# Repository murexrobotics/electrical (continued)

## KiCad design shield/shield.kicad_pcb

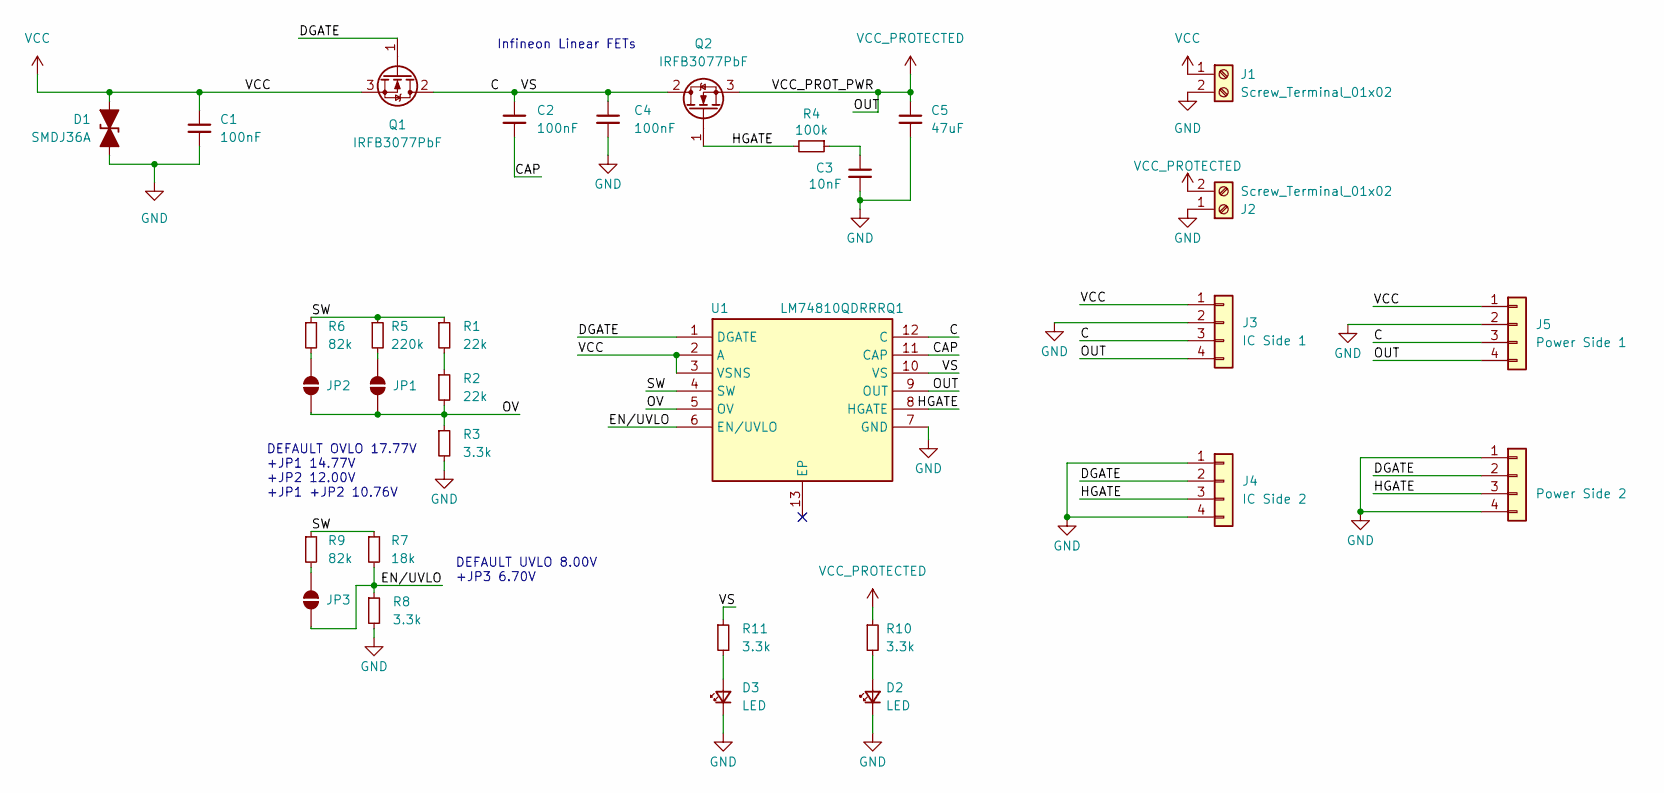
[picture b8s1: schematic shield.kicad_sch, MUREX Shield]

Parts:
C1, C2, C4: 100nF; C_0603_1608Metric
C3: 10nF; C_0603_1608Metric
C5: 47uF; C_1206_3216Metric
D1: SMDJ36A; D_SMC
D2, D3: LED; LED_0603_1608Metric
J1, J2: Screw_Terminal_01x02; TerminalBlock_Phoenix_MKDS-1,5-2-5.08_1x02_P5.08mm_Horizont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
J3: IC Side 1; PinHeader_1x04_P2.54mm_Vertical
J4: IC Side 2; PinHeader_1x04_P2.54mm_Vertical
J5: Power Side 1; PinHeader_1x04_P2.54mm_Vertical
J6: Power Side 2; PinHeader_1x04_P2.54mm_Vertical
JP1, JP2, JP3: SolderJumper_2_Open; SolderJumper-2_P1.3mm_Open_RoundedPad1.0x1.5mm
Q1, Q2: IRFB3077PbF; PG-TO220-3_INF
R1, R2: 22k; R_0603_1608Metric
R3, R8, R10, R11: 3.3k; R_0603_1608Metric
R4: 100k; R_0603_1608Metric
R5: 220k; R_0603_1608Metric
R6, R9: 82k; R_0603_1608Metric
R7: 18k; R_0603_1608Metric
U1: LM74810QDRRRQ1; SON50P300X300X80-13N-D; Manufacturer_Part_Number LM74810QDRRRQ1; Mouser Part Number 595-LM74810QDRRRQ1

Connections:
/C: C2.1, C4.1, J3.3, J5.3, Q1.2 (D), Q2.2 (D), R11.1, U1.10 (VS), U1.12 (C)
/CAP: C2.2, U1.11 (CAP)
/DGATE: J4.2, J6.2, Q1.1 (G), U1.1 (DGATE)
/EN/UVLO: JP3.2 (B), R7.2, R8.1, U1.6 (EN/UVLO)
/HGATE: J4.3, J6.3, Q2.1 (G), R4.2, U1.8 (HGATE)
/OV: JP1.2 (B), JP2.2 (B), R2.2, R3.1, U1.5 (OV)
/SW: R1.1, R5.1, R6.1, R7.1, R9.1, U1.4 (SW)
GND: C1.2, C3.2, C4.2, C5.2, D1.1 (A1), D2.1 (K), D3.1 (K), J1.2, J2.1, J3.2, J4.1, J4.4, J5.2, J6.1, J6.4, R3.2, R8.2, U1.7 (GND)
unnamed: C3.1, R4.1
unnamed: D2.2 (A), R10.2
unnamed: D3.2 (A), R11.2
unnamed: JP1.1 (A), R5.2
unnamed: JP2.1 (A), R6.2
unnamed: JP3.1 (A), R9.2
unnamed: R1.2, R2.1
VCC: C1.1, D1.2 (A2), J1.1, J3.1, J5.1, Q1.3 (S), U1.2 (A), U1.3 (VSNS)
VCC_PROTECTED: C5.1, J2.2, J3.4, J5.4, Q2.3 (S), R10.1, U1.9 (OUT)

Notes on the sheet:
DEFAULT OVLO 17.77V +JP1 14.77V +JP2 12.00V +JP1 +JP2 10.76V
Infineon Linear FETs
DEFAULT UVLO 8.00V +JP3 6.70V

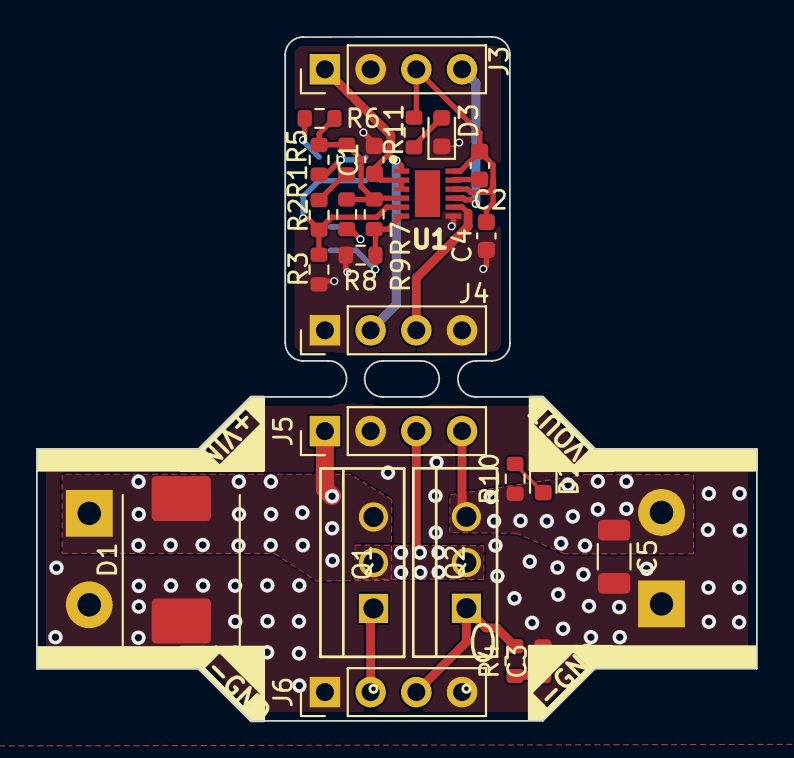
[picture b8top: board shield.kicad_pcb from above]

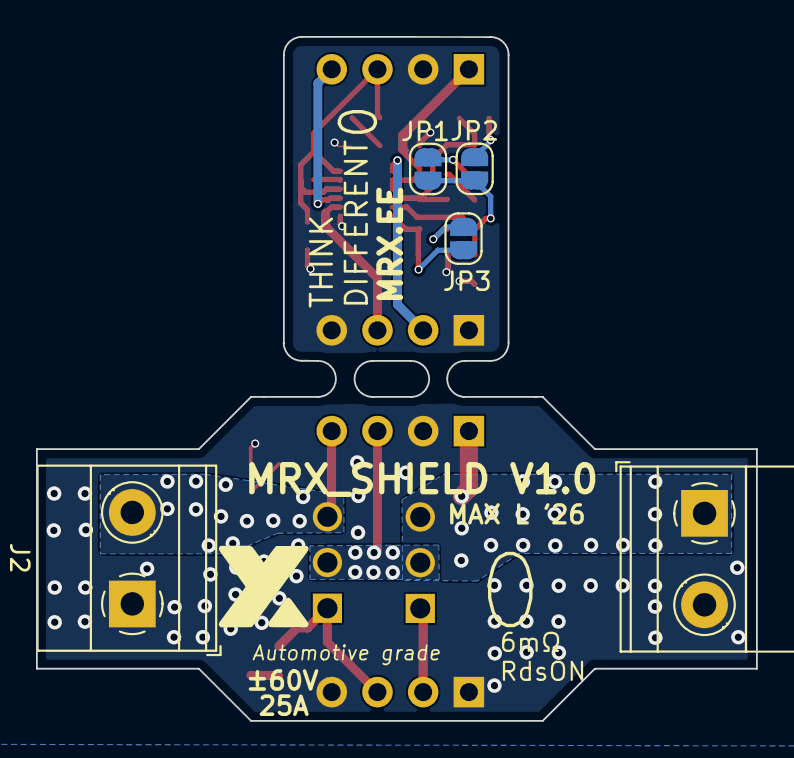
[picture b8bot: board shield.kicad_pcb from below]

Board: 2 copper layers, 40.0 x 38.0 mm, 31 parts (5 on the bottom side), 17 nets.

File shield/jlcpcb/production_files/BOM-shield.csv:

Comment,Designator,Footprint,LCSC
100nF,"C1,C2,C4",C_0603_1608Metric,C14663
SMDJ36A,D1,D_SMC,C152051
LED,D2,LED_0603_1608Metric,C2286
220k,R5,R_0603_1608Metric,C22961
LED,D3,LED_0603_1608Metric,C2297
3.3k,"R10,R11,R3,R8",R_0603_1608Metric,C22978
82k,"R6,R9",R_0603_1608Metric,C23254
100k,R4,R_0603_1608Metric,C25803
18k,R7,R_0603_1608Metric,C25810
22k,"R1,R2",R_0603_1608Metric,C31850
LM74810QDRRRQ1,U1,SON50P300X300X80-13N-D,C3215601
10nF,C3,C_0603_1608Metric,C57112
47uF,C5,C_1206_3216Metric,C76659

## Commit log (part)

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2023-05-05 Feat: Created ESC Project
2023-05-05 Fix: Fix ESC project layout
2023-05-06 Feat: created CM4 schematic with modifications to fit needs
2023-05-07 Fix: added ds_store and auto save files to gitignore
2023-05-07 Feat: Added BMI088 to library
2023-05-07 Feat: added MMC5603NJ library
2023-05-07 Feat: carrier board synchronized footprints with schematic
2023-05-07 Feat: Attempted to add TPS568230 library (+ custom symbol)
2023-05-07 Fix: added footprint of TPS568230
2023-05-07 Feat: Removed TPS568230, added TPS568215RNNR symbol to library
2023-05-07 Fix: added whitespace in readme
2023-05-07 Feat: Added RP2040 (not connected yet), connectors
2023-05-07 Feat: initialized PLC project
2023-05-10 Feat: Added LTC4352 Symbol and Footprint
2023-05-10 Fix: Reworked LTC4352 Symbol
2023-05-11 Feat: Added Application Circuit for LTC4352
2023-05-12 Fix: added jumpers to all i2c sensors
2023-05-12 Feat: Configured VOUTs for both TPS568215s
2023-05-13 Feat: draft of ESC carrier board schematic
2023-05-13 Refactor: deleted unused hierarchical schematics
2023-05-14 Refactor/Feat: refactored projects into networking folder and created rj45_breakout project
2023-05-14 Fix: relinked footprints
2023-05-15 Feat: Added 01x03 Conn. for Power to ESC_Carrier
2023-05-15 Refactor: Moved bucks into hierarchical schematics
2023-05-15 Feat: begun work on carrier pcb and imported NGFF m.2 library
2023-05-16 Feat: imported m.2 connector and more work on carrier board
2023-05-16 Feat: organized PCB file, preparing for layout and routing.
2023-05-16 Fix: Altered M.2 Pinout
2023-05-17 Feat: Added Custom Softstarter Circuitry (C&R TBC)
2023-05-18 Feat: Added draft resistance and capacitance to softstarter
2023-05-19 Feat: Added ACS712 Current Sensor
2023-05-19 Feat: progress routing usb and hdmi
2023-05-19 Fix: added rounded corners and a few minor fixes
2023-05-20 Feat: more routing with i2c and gpio
2023-05-21 FEAT: added fuses to ESC Carrier
2023-05-22 FEAT: added efuses to ESC Carrier
2023-05-22 Refactor: moved custom symbol to library file
2023-05-23 feat: carrier board layout v2
2023-05-29 Feat: routed non-important traces on carrier board
2023-05-30 Feat: power line routing, marked down necessary revisions, rerouted i2c
2023-05-30 Feat: updated efuse symbol and assigned some footprints
2023-06-04 Fix: updated esc carrier to esc connectors
2023-06-04 Feat: impedanced matched traces calculations entered into net classes
2023-06-04 Feat: routed differential pairs. 90 more routes to go
2023-06-05 Fix: added phases to esc to esc carrier connector
2023-06-05 Feat: added test points
2023-06-05 Feat: updated esc to esc carrier connector, updated test points
2023-06-05 Refactor: component orientation
2023-06-05 Feat: conforms to jlc specs and (mostly) kicad DRC
2023-06-06 Feat: added murex font
2023-06-06 Feat: initial placement of components
2023-06-07 Feat: added silkscreen
2023-06-07 Feat: semi-baked adc implementation
2023-06-09 Feat: added some traces between components
2023-06-15 Feat: linked up majority of components to lcsc parts
2023-06-16 Feat: fixes all around, refactored project and working on CM4 POS file
2023-06-16 Refactor: re-annotated schematic with cm4 connector POS configured
2023-06-17 Feat: major revamps to pcb, finished bom and pos
2023-06-19 Feat: tidied up carrier board, added 3d models, fully prepared for production
2023-06-19 Feat: worked on ESC Carrier board
2023-06-20 Feat: Completed footprint assignment, began part placement
2023-06-20 Feat: small changes to carrier (i think units?)
2023-06-21 Feat: Finished layout for individual ICs
2023-06-24 Feat: Added 282836-2 (Backup Screw Term. to Carrier)
2023-06-25 Feat: finished routing esc carrier
2023-06-25 Feat: cleaned up traces and zones, adjusted trace widths
2023-06-26 Feat: Added copper zones for voltage regulation
2023-06-26 Fix: Minor Schematic Changes
2023-06-26 Feat: More routing and component rearranging
2023-06-26 Fix: Removed pull up resistors
2023-06-27 Feat: Finished routing
2023-06-28 Fix: added ADC I2C address to back silk
2023-07-03 Feat: 🎉🙏 carrier board v1 sent to production
2023-07-03 Fix: replace jlcpcb part no for R11 and R12
2023-07-03 Feat: Switched WAGO 2606-1103 to MOLEX 0430450821
2023-07-03 Feat: Reduced inductor pad size
2023-07-03 Feat: Deleted all traces, zones, and edge cuts
2023-07-04 Feat: routed traces
2023-07-04 Feat: routed phases
2023-07-04 Feat: carrier board v1.1 release and production
2023-07-04 Feat: generating v1.1 carrier board
2023-07-04 Revert "Feat: added vias"
    This reverts commit d9f0b0a7b740c1a5059e2e7f1ed87a6101a3388b.
2023-07-05 Feat: Basic silkscreening
2023-07-05 Feat: switched phase connector to microfit, updated esc connector pinout, updated component layout
2023-07-06 Feat: Updated board constraints, fixed various violations
2023-07-06 Feat: Added jumper for INA226
2023-07-07 Feat: Finished bom and cpl, generated gerbers
2023-07-10 Fix[carrier v1.2]: updated 5V zone for m.2
2023-07-11 Feat: Changed microfit pinout, added copper zone over vin
2023-07-11 Feat: Increased voltage output to 5.1V, edited back silkscreen
2023-07-11 Refactor: organized escs
2023-07-12 Fix: updated uart connections to carrier board
2023-07-12 Feat: initialized rp2040 esc and 5530843-7 card edge footprint
2023-07-14 Feat: Restructured labels, fixed nmos polarity, rerouted board
2023-07-15 Feat: Switched to Molex Megafit, Rerouting, Updated Silkscreen
2023-07-15 Feat: Updated schematic, minor silkscreen edits
2023-07-15 Feat: removed 7 ntc thermistors
2023-07-16 Feat: Created AGND islands
2023-07-16 Fix[carrier1.2]: kicad wants rotation?
2023-07-18 Feat: switched thermistor to AS32_1R030, minor fixes
2023-07-20 Feat: Removed ACS712 and M.2 Conn
2023-07-20 Feat: Broke out I2C
2023-07-20 Feat: created production files
2023-07-22 Feat: Powerboard sent to chinese production
2023-07-24 Feat: added 3d models
2023-07-29 Feat[esc]: schematic to pcb placement of B-G431B-ESC1 + RP2040
2023-07-29 Feat[stesc]: refactored project and finished draft
2023-08-03 Feat[esc_carrier 1.1]: refactored pinout to esc, made board smaller
2023-08-03 Fix: removed esc_carrier v1.0, removed blender files
2023-08-17 Feat[drvesc]: Established basic gate driver architecture
2023-08-18 Feat[bmi088 breakout]: design complete
2023-08-18 Feat[bme680 breakout]: design complete
2023-08-18 Feat[pca9585 breakout]: design complete
2023-08-19 Feat: Finished RP2040 control system
2023-08-20 Feat[drvesc]: Draft routing
2023-08-21 Feat[esc_carrier v2.0]: v2.0 production ready
2023-08-23 Feat[power]: Added LED 3D models
2023-08-24 Feat[drvesc]: updated card edge pinout
2023-08-25 Feat[drvesc]: Minor rerouting and positioning
2023-08-31 Feat[switch]: added IP175G symbol
2023-08-31 Feat[switch]: added sheet metadata and magnetics symbols to sch
2023-08-31 Feat[switch]: further work on schematic
2023-08-31 Fix[switch]: renamed quad to dual transformer
2023-09-01 Feat[anyesc]: initialized project
2023-09-01 Feat[switch]: unpolished schematic complete
2023-09-01 Feat[drvesc]: minor silkscreen edit
2023-09-01 Refactor[switch]: net labels and reorganisation
2023-09-01 Feat[switch]: created all necessary symbols and footprints, started PCB
2023-09-02 Feat[switch]: initial board layout (FOLLOW @TODOs)
2023-09-03 Feat[anyesc]: anyesc design complete
2023-09-16 Feat[switch]: initial routes
2023-09-25 Feat[switch]: Minor rerouting
2023-09-29 Feat[switch]: rotated J1
2023-10-06 Feat[breakouts]: created ina226 breakout schematic v1.0
2023-10-07 Feat[breakouts]: Fixed listed problems with ina226 breakout
2023-10-07 Feat[breakouts]: Separated A1/A0 from main chip schem
2023-10-07 Fix[ina226 breakout]: removed lock file
2023-10-08 Feat[switch]: Fixed single transformer footprint, added 3d models
2023-10-08 Feat[switch]: Added diode, initial silkscreen
2023-10-09 Feat[breakouts]: Created PCB layout, some ratsnest untangling
2023-10-09 Feat[breakouts]: Finished PCB layout for INA226
2023-10-09 Feat[breakouts]: Finished PCB layout for INA226, added traces
2023-10-10 Feat[breakouts]: Modified PCB layout, added some traces
2023-10-12 Feat[breakouts]: Added via stitching, rearranged some components, added copper pours
2023-10-16 Chore[bmi088 breakout]: bumped to new kicad version
2023-10-16 Chore[carrier]: bumped to new kicad version
2023-10-18 Feat[breakouts]: Moved header pins, added silk labelling, fixed 3d model?
2023-10-18 Feat[drvesc]: Tapeout
2023-10-18 Feat[anyesc]: tapeout
2023-10-19 Feat[breakouts]: Fixed silk, increased board size
2023-10-30 Anyesc tape out (panelization needs fixing)
2023-10-30 Feat[breakouts]: started ADC schematic
2023-10-30 Fix[anyesc]: panelization
2023-11-03 Feat[switch]: Minor fixes for tapeout
2023-11-10 Feat: Updated T3 part, ordered switch
2023-11-21 Feat[drvesc]: Fixed clearance violations
2023-11-25 Feat[carrier]: v3 schematic progress (esp32, general cleanup/refactoring)
2023-11-26 Feat[carrier]: v3 schematic draft complete
2023-11-26 Feat[power]: finished dual buck ic sheet
2023-11-26 Feat[carrier]: v3 pcb initialized
2023-11-27 Feat[power]: v2 schematic draft complete
2023-11-28 Feat[carrier]: component mapping complete
2023-11-28 Feat[breakouts]: Fixed some ToDOs
2023-11-28 Feat[carrier]: 99% taped out, silkscreening done, added new 3.3v buck
2023-11-29 Fix[carrier]: switch bmi088 to i2c mode
2023-11-29 Fix[carrier]: current adjustments
2023-11-30 Feat[carrier]: v3 wrapping up
2023-11-30 Feat[power]: initial layout
2023-12-02 Feat[power]: routing and silkscreening
2023-12-04 Feat[power]: component mapping
2023-12-09 Feat[power]: V2 ordered
2023-12-11 Fix[carrier]: fix i2c pull up resistor jlc mapping
2024-01-03 Feat: making SID
2024-02-11 Fix: added esc carrier back
2024-03-06 Feat: added MUREX Shield schematic
2024-03-06 Feat(shield): ready for routing
2024-03-07 Feat(shield): initial routing
2024-03-07 Fix: revised shield schematic and pcb
2024-03-09 Fix: fixed some labels
2024-04-04 Fix: panelized shield
2024-05-08 Feat: working on web demo
2024-05-21 feat[card]: worlds business card design
2024-06-02 feat[switch]: V2 tapeout
2024-06-07 feat[switch]: V2 info update
2024-06-23 Fix link to network switch docs
2024-08-13 Feat[power2]: initial design
2024-09-29 Feat[power2]: first draft
2024-10-08 Feat[Smart Power Board]: Initial Schematic
2024-10-08 Feat[minifoc, devesc]: begin schematic
2024-10-13 Feat[minifoc_esc]: board layout planning
2024-10-13 Feat[shield]: PCB draft complete
2024-10-14 Feat[shield]: Ready for tapeout
2024-10-17 Feat[SmartPowerBoard]: MCU Development
2024-10-21 Feat[shield]: sent to JLC production
2024-10-22 Feat[SmartPowerBoard]: IDC development
2024-10-23 Fix[electrical]: resolve 8.99 pcb_text crash
2024-10-24 Feat[SmartPowerBoard]: MCU Implementation
2024-10-30 Feat[SmartPowerBoard]:Starting Board Layout
2024-10-30 Feat[minifoc_esc]: draft PCB
2024-11-04 Feat[SmartPowerBoard]: OLED Display Layout
2024-11-06 Feat[minifoc_esc]: v1 tapeout
2024-11-16 Feat[minifoc_esc]: production ready
2024-11-18 Feat[SmartPowerBoard]: Layout
2024-11-27 Feat[SmartPowerBoard]: Mid-Progress Update
2024-11-27 Feat[SmartPowerBoard]: New Layout
2024-11-30 Feat[SmartPowerBoard]: Organized Schematic and New Buck
2024-12-02 Feat[SmartPowerBoard]: More Routing
2024-12-07 Feat[SmartPowerBoard]: Silkscreen + Ground
2024-12-14 Feat[SmartPowerBoard]: Fixing Layout
2024-12-14 Feat[SmartPowerBoard]: DRC Errors Fixed
2024-12-15 Feat[SmartPowerBoard]: Silkscreen done
2024-12-31 Feat[navboard]: Sensor Schematic
2025-01-09 Feat[navboard]: Additional Sensors Schematic
2025-01-19 Feat[navboard]: Breakout of Different Sensors
2025-06-16 Feat[2025_SID]: Update topside
2025-06-30 Feat[SmartPowerBoard]: update 3d models
2025-07-16 Fix: remove bom/cpl from gitignore
2025-11-12 Feat[float_carrier_2025-2026]: start
2025-11-23 Feat[float_carrier_2025-2026]: connectors and buck converter added to schematic
2025-11-24 Feat[float_carrier_2025-2026]:higher power buck, breakout header pins, labels added
2025-12-25 Feat[float_carrier_2025-2026]:connectors 3D symbol fixed, edge cut fixed
2026-02-21 Feat[float_carrier_2025-2026]
    dimensions changed, hole position changed, board smaller.
2026-03-13 Feat[Fatpower]: Add 5V Buck Schematic
2026-03-16 Feat[Fatpower]: Add 3.3V Buck Schematic, Vin/Vout pin of buck fixed, power connectors of navigator board/ethernet switch added
